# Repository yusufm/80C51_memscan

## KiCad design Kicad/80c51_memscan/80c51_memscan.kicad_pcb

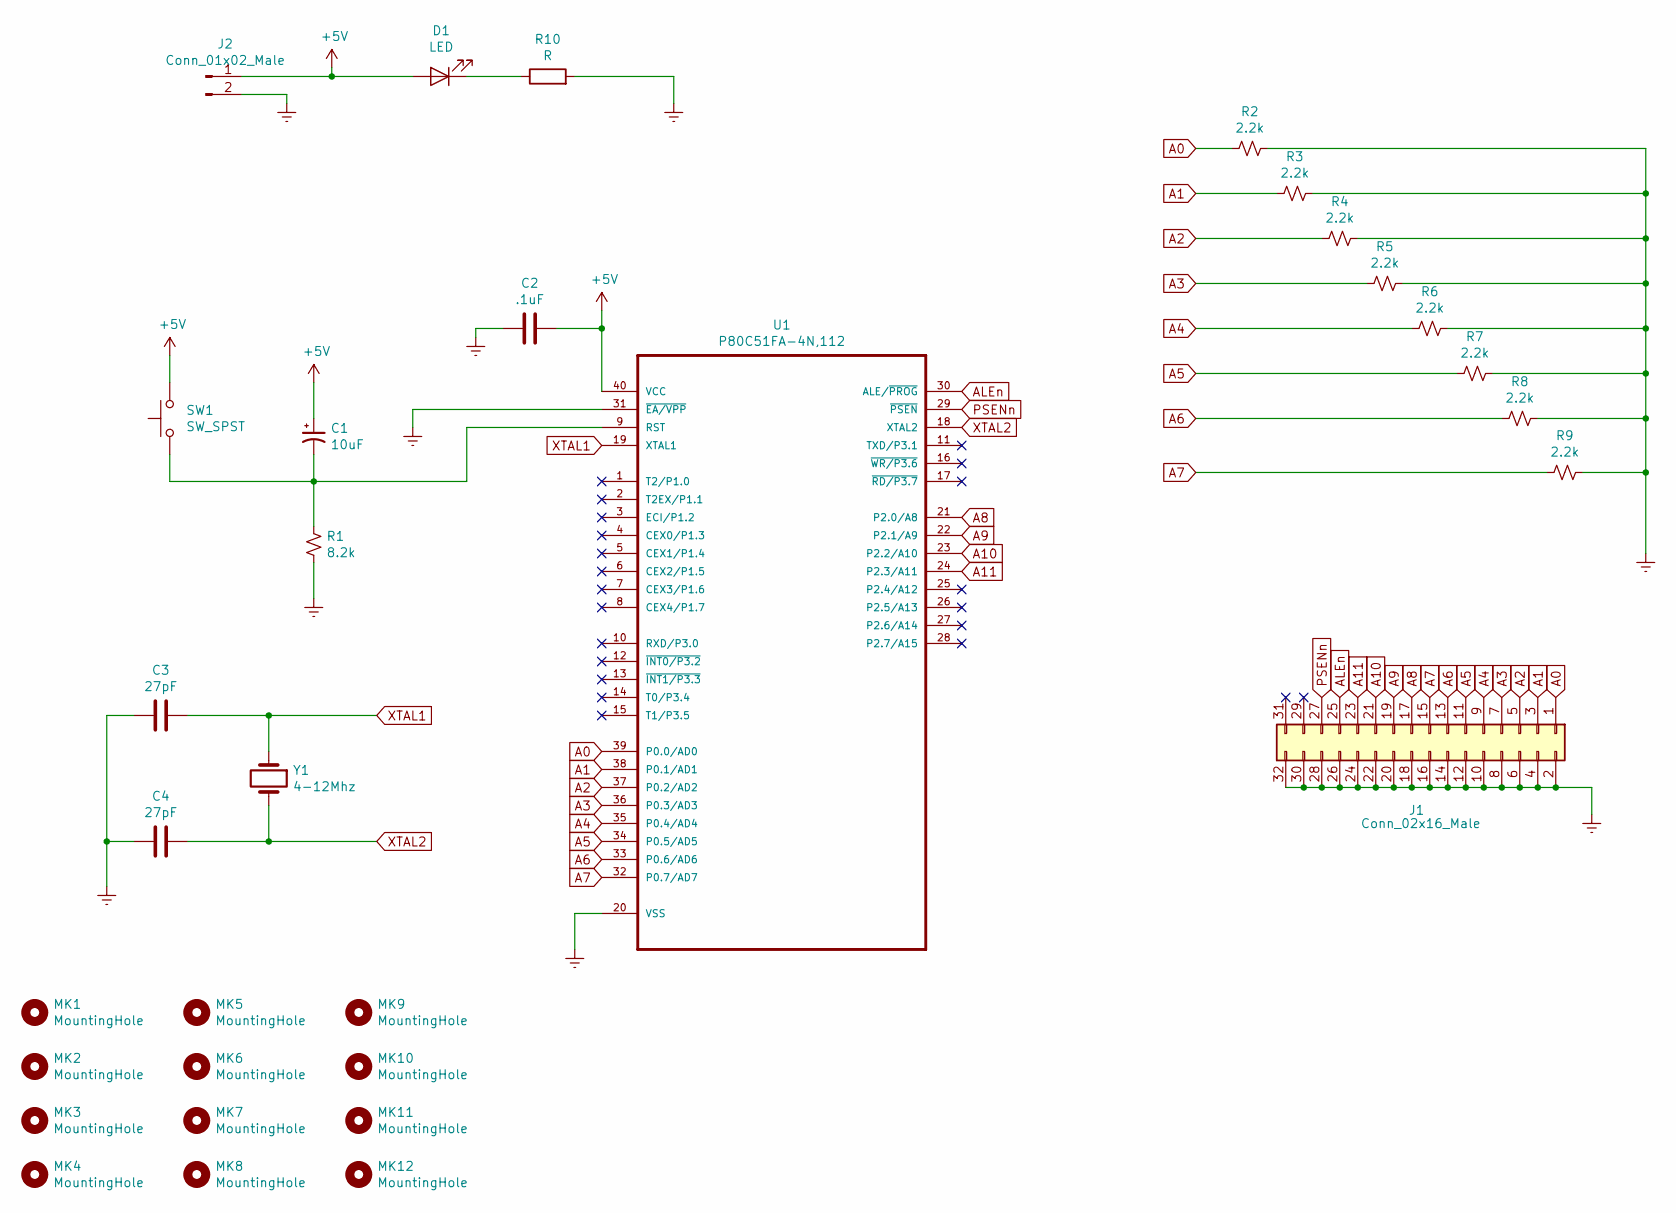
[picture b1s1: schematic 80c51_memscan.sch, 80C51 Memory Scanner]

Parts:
C1: 10uF; C_0603_1608Metric_Pad1.05x0.95mm_HandSolder
C2: .1uF; C_0603_1608Metric_Pad1.05x0.95mm_HandSolder
C3, C4: 27pF; C_0603_1608Metric_Pad1.05x0.95mm_HandSolder
D1: LED; LED_0603_1608Metric_Pad1.05x0.95mm_HandSolder
J1: Conn_02x16_Male; PinHeader_2x16_P2.54mm_Vertical
J2: Conn_01x02_Male; Molex_KK-254_AE-6410-02A_1x02_P2.54mm_Vertical
MK1, MK2, MK3, MK4, MK5, MK6, MK7, MK8, MK9, MK10, MK11, MK12: MountingHole; MountingHole_8.4mm_M8
R1: 8.2k; C_0603_1608Metric_Pad1.05x0.95mm_HandSolder
R2, R3, R4, R5, R6, R7, R8, R9: 2.2k; C_0603_1608Metric_Pad1.05x0.95mm_HandSolder
R10: R; C_0603_1608Metric_Pad1.05x0.95mm_HandSolder
SW1: SW_SPST; SW_SPST_B3S-1000
U1: P80C51FA-4N,112; DIP254P1524X470-40
Y1: 4-12Mhz; Crystal_SMD_0603-2Pin_6.0x3.5mm_HandSoldering

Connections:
+5V: C1.1, C2.2, D1.2 (A), J2.1, SW1.2, U1.40 (VCC)
A0: J1.1, R2.2, U1.39 (P0.0/AD0)
A1: J1.3, R3.2, U1.38 (P0.1/AD1)
A2: J1.5, R4.2, U1.37 (P0.2/AD2)
A3: J1.7, R5.2, U1.36 (P0.3/AD3)
A4: J1.9, R6.2, U1.35 (P0.4/AD4)
A5: J1.11, R7.2, U1.34 (P0.5/AD5)
A6: J1.13, R8.2, U1.33 (P0.6/AD6)
A7: J1.15, R9.2, U1.32 (P0.7/AD7)
A8: J1.17, U1.21 (P2.0/A8)
A9: J1.19, U1.22 (P2.1/A9)
A10: J1.21, U1.23 (P2.2/A10)
A11: J1.23, U1.24 (P2.3/A11)
ALEn: J1.25, U1.30 (ALE/~PROG)
Earth: C2.1, C3.2, C4.2, J1.2, J1.4, J1.6, J1.8, J1.10, J1.12, J1.14, J1.16, J1.18, J1.20, J1.22, J1.24, J1.26, J1.28, J1.30, J1.32, J2.2, R1.2, R2.1, R3.1, R4.1, R5.1, R6.1, R7.1, R8.1, R9.1, R10.2, U1.20 (VSS), U1.31 (~EA/VPP)
unnamed: C1.2, R1.1, SW1.1, U1.9 (RST)
unnamed: D1.1 (K), R10.1
PSENn: J1.27, U1.29 (~PSEN)
XTAL1: C3.1, U1.19 (XTAL1), Y1.1
XTAL2: C4.1, U1.18 (XTAL2), Y1.2

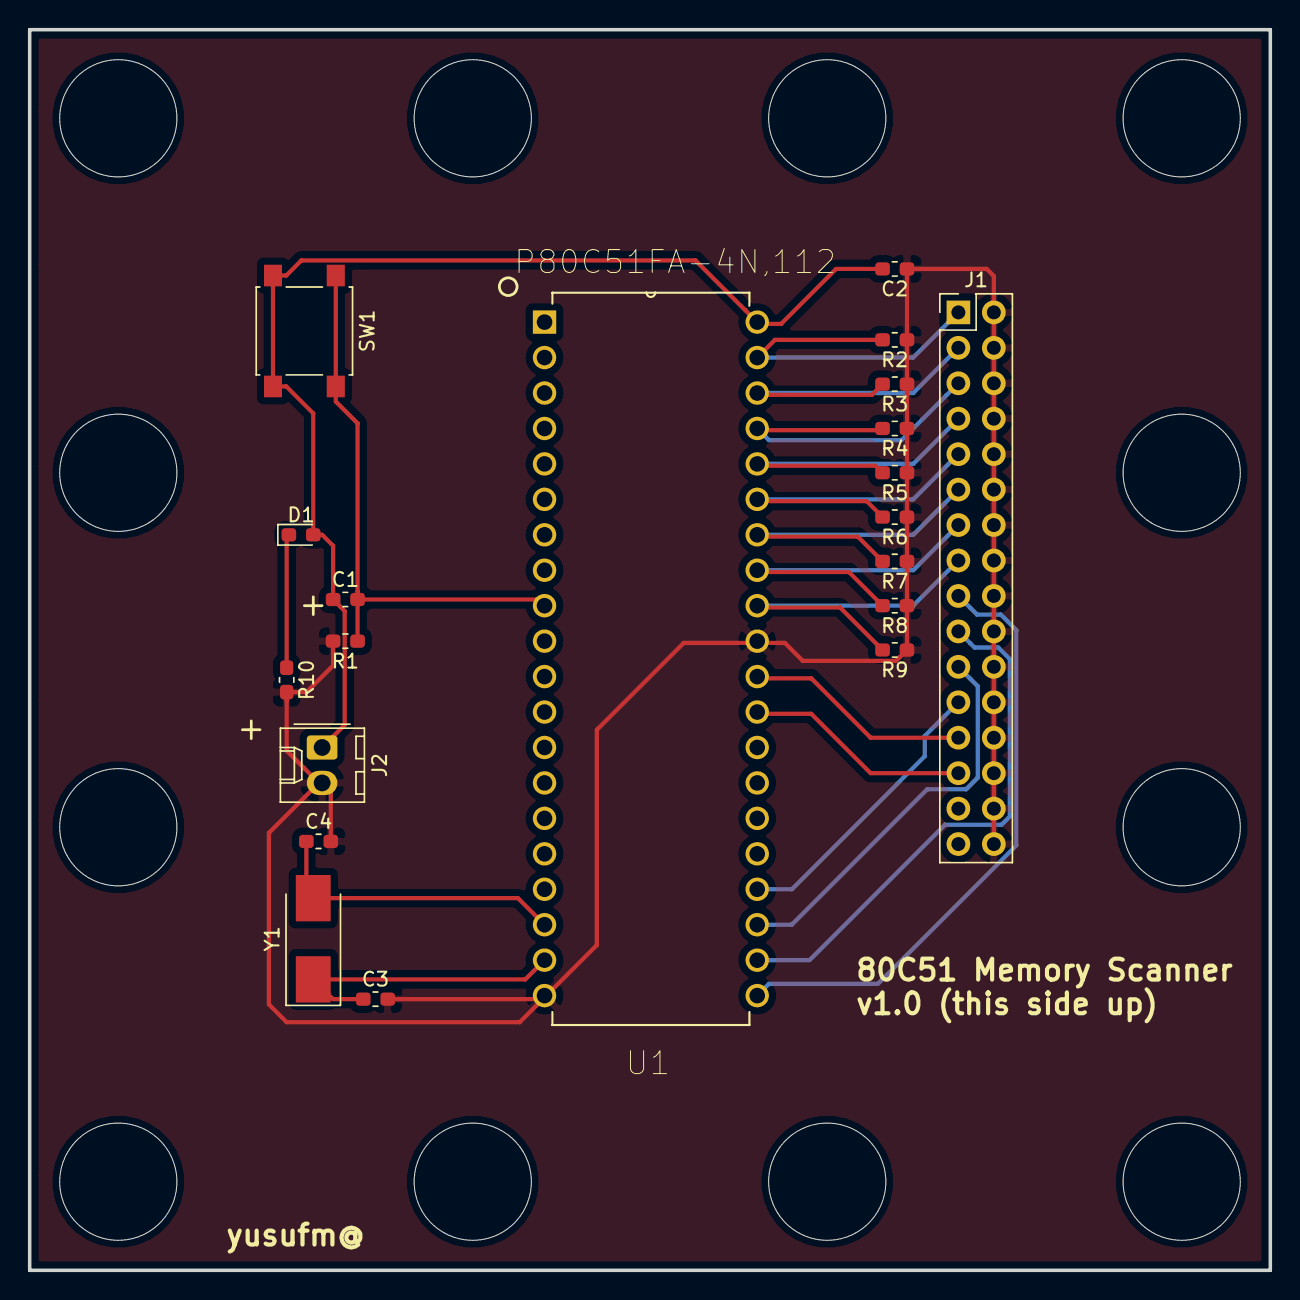
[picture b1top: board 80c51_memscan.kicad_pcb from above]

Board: 2 copper layers, 88.9 x 88.9 mm, 32 parts (0 on the bottom side), 20 nets.

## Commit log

2019-08-31 Initial schematic.
2019-09-05 Folding in feedback and using correct symbol footprint: https://www.snapeda.com/parts/P80C51FA-4N%2C112/NXP%20USA%20Inc./view-part/?ref=search&t=80c51
2019-09-05 Added power connector pins.
2019-09-05 Fixing typo 8051c -> 80c51.
2019-09-06 Folding in feedback. Adding led and additional pins to header.
2019-09-06 Fix J1 text.
2019-09-06 Fixing bad cap wiring and some net names.
2019-09-07 Fixed switch symbol in schematic. And associated footprints for components.
2019-09-07 Associated footprints. Starting pcb layout.
2019-09-07 Fixes and changes to needed to get the PCB going (change J1 symbol to match footprints. Mounting holes added to schematic to match PCB requirements, etc.
2019-09-07 Initial PCB layout complete.
2019-09-07 Changed the switch to be push button.
2019-09-07 Adding text.
2019-09-08 Added caps to xtal.
2019-09-09 Fix minor typo.
